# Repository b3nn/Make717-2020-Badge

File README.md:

# Make717 2020 Badge
Soldering Badge for Make717

Designed for the children's soldering event at Lancaster Science Factory in March 2020. 

Black Mask, White Silkscreen, reverse mounted slow flash LEDs

[]

[]

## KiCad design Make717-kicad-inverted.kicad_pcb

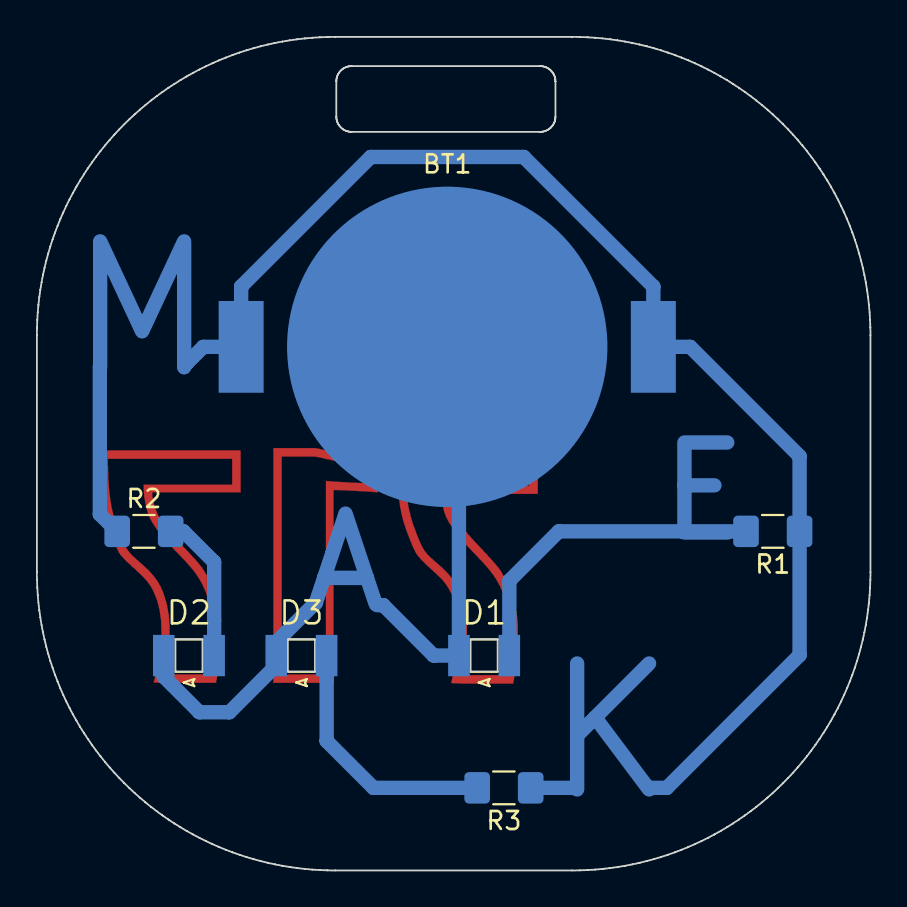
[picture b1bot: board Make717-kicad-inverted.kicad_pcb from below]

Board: 2 copper layers, 46.3 x 46.3 mm, 7 parts (7 on the bottom side), 5 nets.

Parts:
BT1: Battery_Cell; linx-bat-hld-001
D1, D2, D3: LED; LED_0807
R1, R2, R3: R; R_1206_3216Metric_Pad1.42x1.75mm_HandSolder

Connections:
GND: BT1.2, D1.1, D2.1, D3.1
unnamed: BT1.1, R1.1, R2.1, R3.1
unnamed: D1.2, R1.2
unnamed: D2.2, R2.2
unnamed: D3.2, R3.2

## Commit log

2020-02-02 Uploading items for KiCad 5.1.5-3
2020-02-02 Updated Pictures and info
2020-02-05 Files for AfterDark version
